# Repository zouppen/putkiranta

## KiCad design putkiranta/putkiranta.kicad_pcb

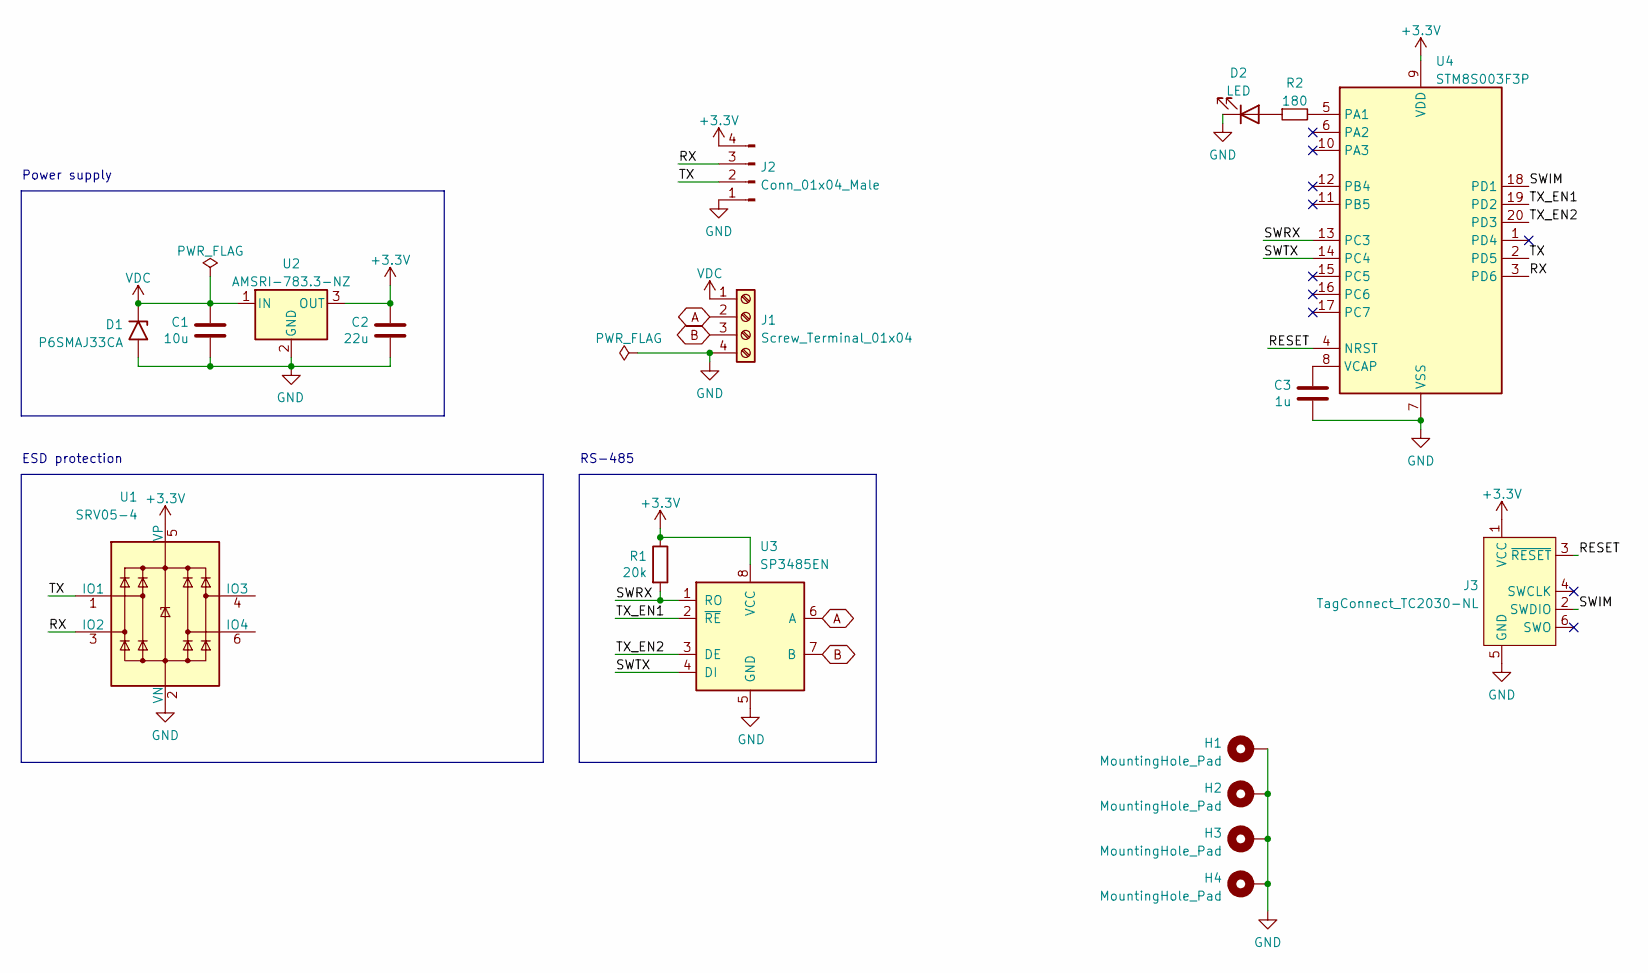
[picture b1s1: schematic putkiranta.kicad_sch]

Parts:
C1: 10u; C_1206_3216Metric; LCSC C13585
C2: 22u; C_0603_1608Metric; LCSC C59461
C3: 1u; C_0603_1608Metric; LCSC C15849
D1: P6SMAJ33CA; D_SMA_Handsoldering; LCSC C3019524
D2: LED; LED_0805_2012Metric; LCSC C2297
H1, H2, H3, H4: MountingHole_Pad; MountingHole_3.2mm_M3_Pad_Via
J1: Screw_Terminal_01x04; PhoenixContact_MCV_1,5_4-G-3.5_1x04_P3.50mm_Vertical
J2: Conn_01x04_Male; JST_PH_B4B-PH-K_1x04_P2.00mm_Vertical
J3: TagConnect_TC2030-NL; Tag-Connect_TC2030-IDC-NL_2x03_P1.27mm_Vertical
R1: 20k; R_0603_1608Metric; LCSC C4184
R2: 180; R_0603_1608Metric; LCSC C22828
U1: SRV05-4; SOT-23-6; LCSC C85364
U2: AMSRI-783.3-NZ; Converter_DCDC_RECOM_R-78E-0.5_THT
U3: SP3485EN; SOIC-8_3.9x4.9mm_P1.27mm; LCSC C8963
U4: STM8S003F3P; TSSOP-20_4.4x6.5mm_P0.65mm; LCSC C52717

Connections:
+3.3V: C2.1, J2.4, J3.1 (VCC), R1.1, U1.5 (VP), U2.3 (OUT), U3.8 (VCC), U4.9 (VDD)
/RESET: J3.3 (~RESET), U4.4 (NRST)
/RX: J2.3, U1.3 (IO2), U4.3 (PD6)
/SWIM: J3.2 (SWDIO), U4.18 (PD1)
/SWRX: R1.2, U3.1 (RO), U4.13 (PC3)
/SWTX: U3.4 (DI), U4.14 (PC4)
/TX: J2.2, U1.1 (IO1), U4.2 (PD5)
/TX_EN1: U3.2 (~RE), U4.19 (PD2)
/TX_EN2: U3.3 (DE), U4.20 (PD3)
A: J1.2, U3.6 (A)
B: J1.3, U3.7 (B)
GND: C1.2, C2.2, C3.2, D1.2 (A2), D2.1 (K), H1.1, H2.1, H3.1, H4.1, J1.4, J2.1, J3.5 (GND), U1.2 (VN), U2.2 (GND), U3.5 (GND), U4.7 (VSS)
unnamed: C3.1, U4.8 (VCAP)
unnamed: D2.2 (A), R2.1
unnamed: R2.2, U4.5 (PA1)
VDC: C1.1, D1.1 (A1), J1.1, U2.1 (IN)

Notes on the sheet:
Power supply
RS-485
ESD protection

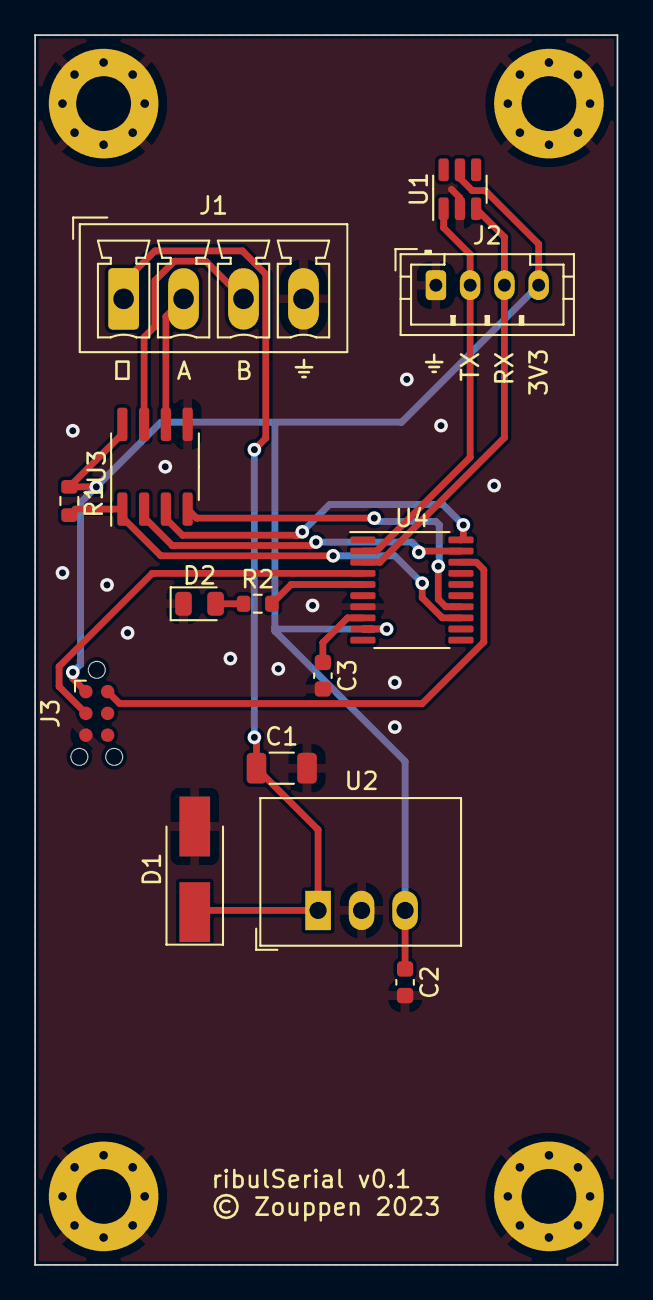
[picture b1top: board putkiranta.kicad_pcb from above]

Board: 2 copper layers, 34.0 x 71.8 mm, 18 parts (0 on the bottom side), 16 nets.

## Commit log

2023-10-02 Minimal boilerplate for STM8S build
2023-10-02 Initial PCB v0.1
2023-10-02 Take the example from https://github.com/jukkas/stm8-sdcc-examples/blob/master/uart/uart.c
